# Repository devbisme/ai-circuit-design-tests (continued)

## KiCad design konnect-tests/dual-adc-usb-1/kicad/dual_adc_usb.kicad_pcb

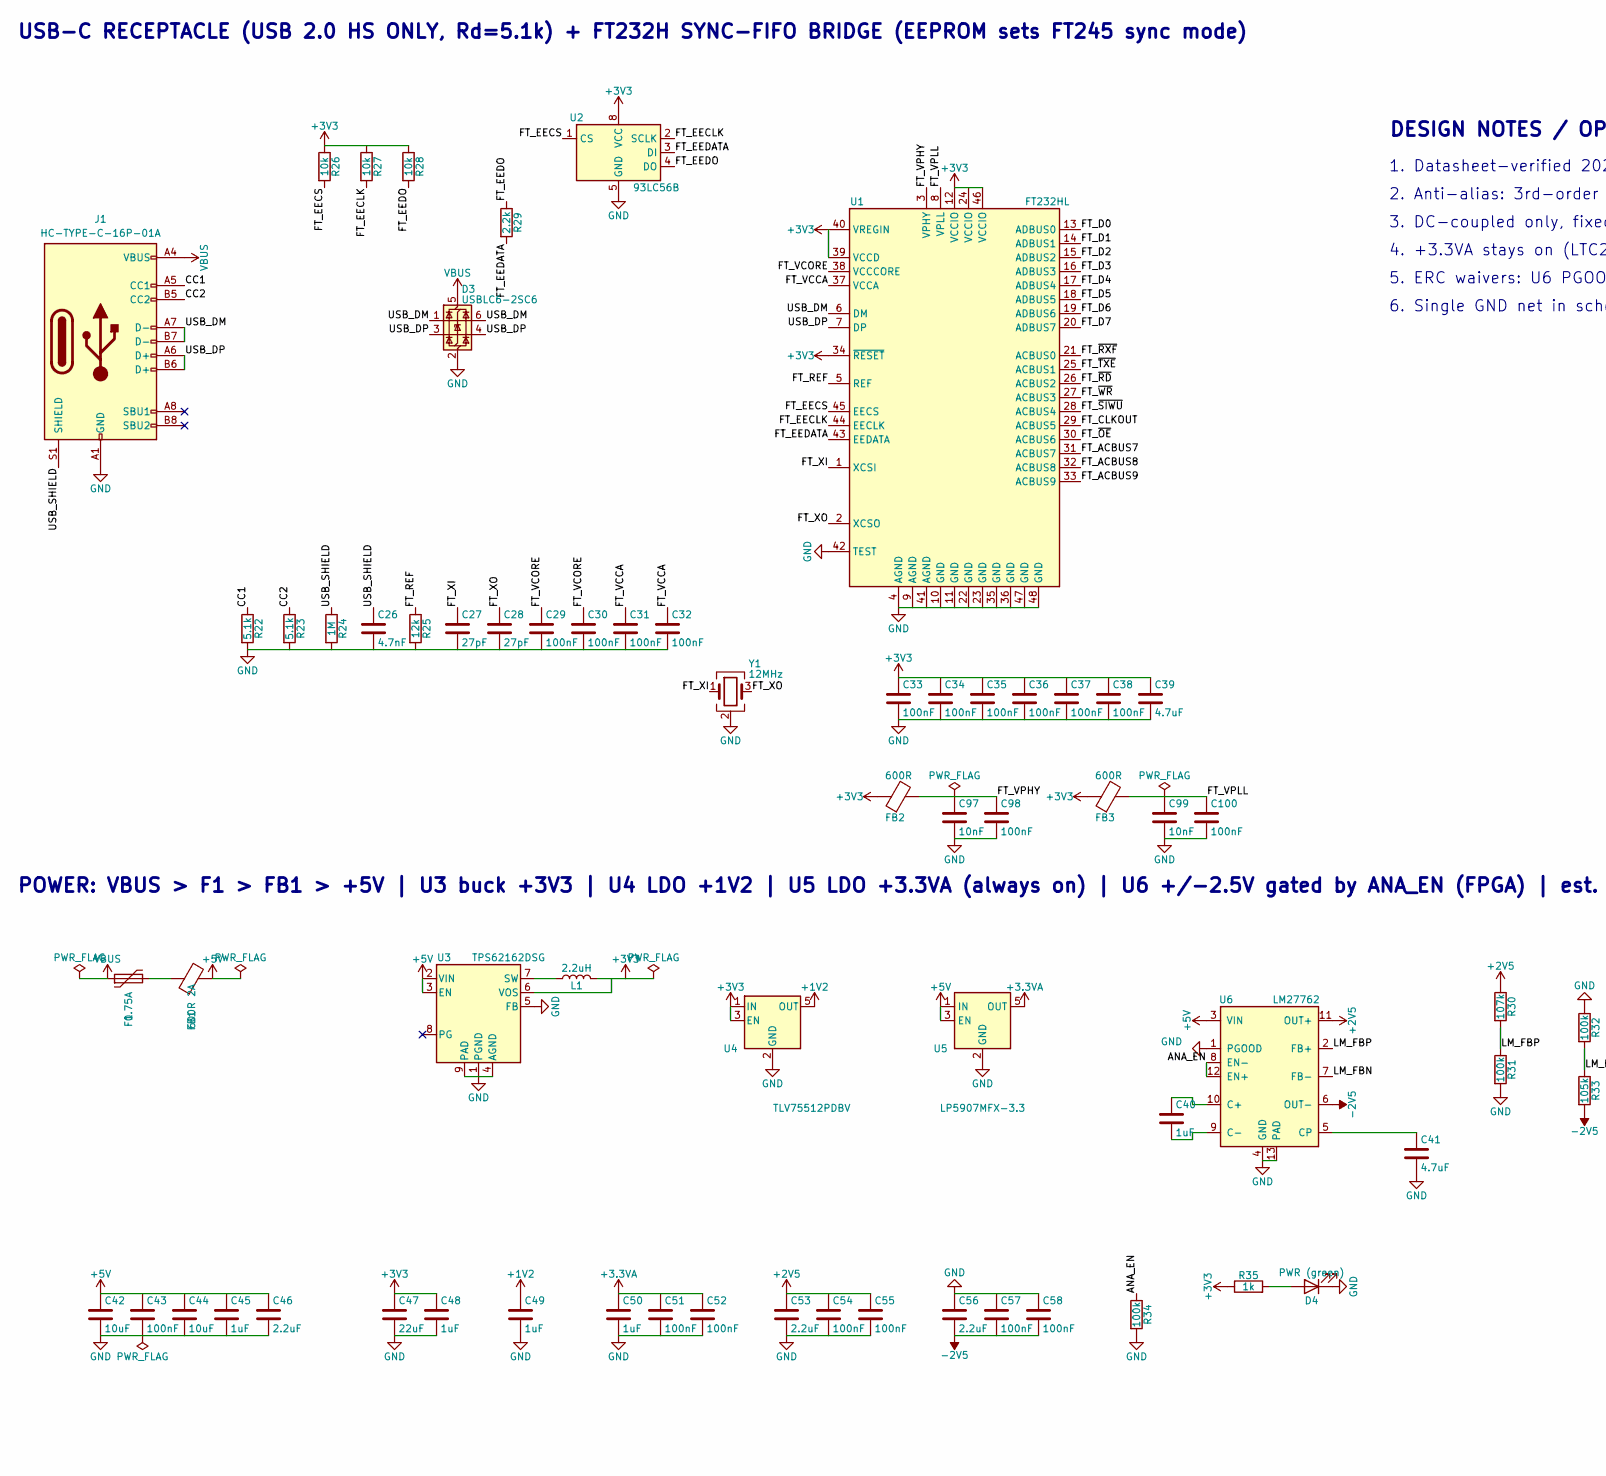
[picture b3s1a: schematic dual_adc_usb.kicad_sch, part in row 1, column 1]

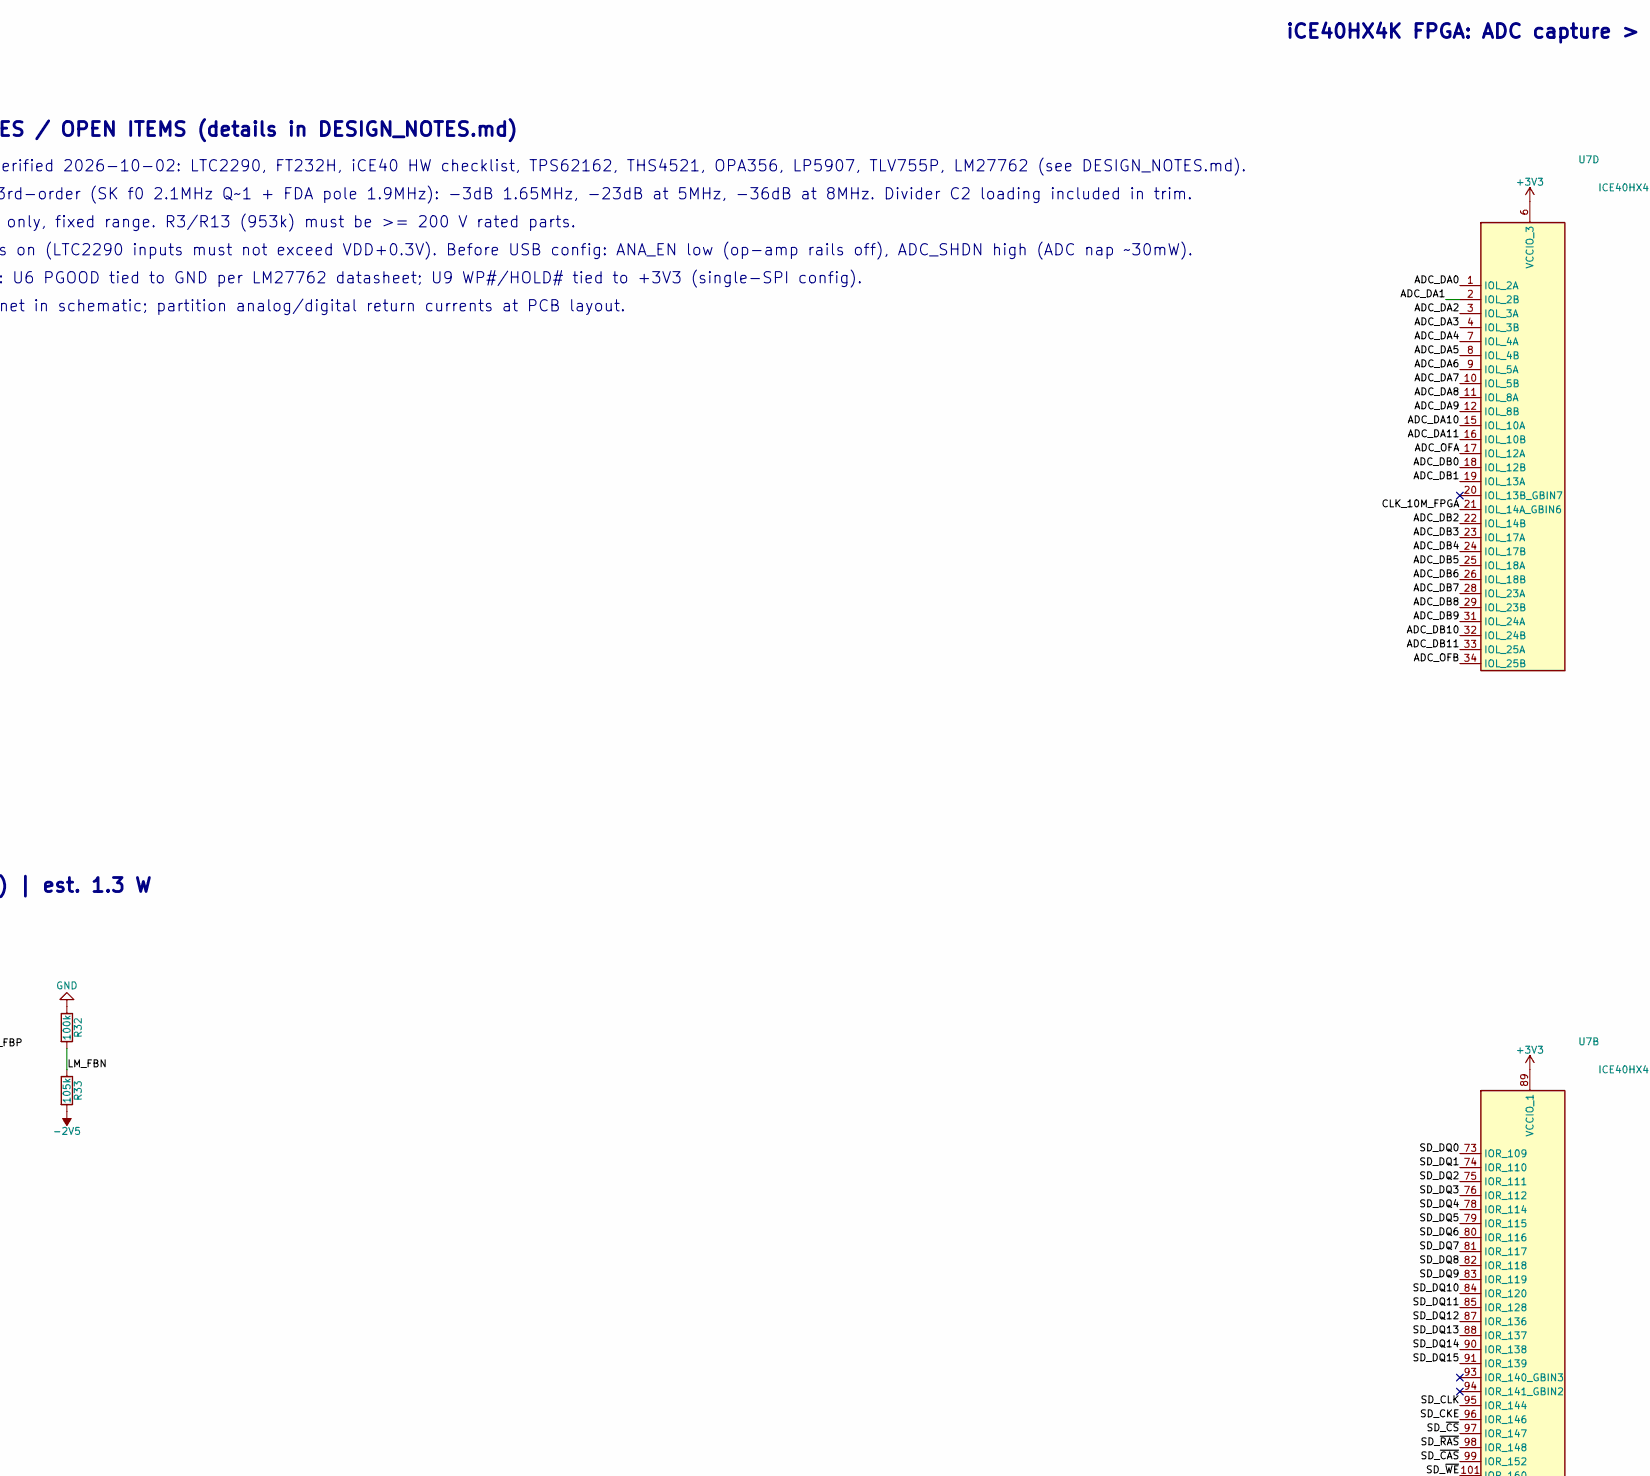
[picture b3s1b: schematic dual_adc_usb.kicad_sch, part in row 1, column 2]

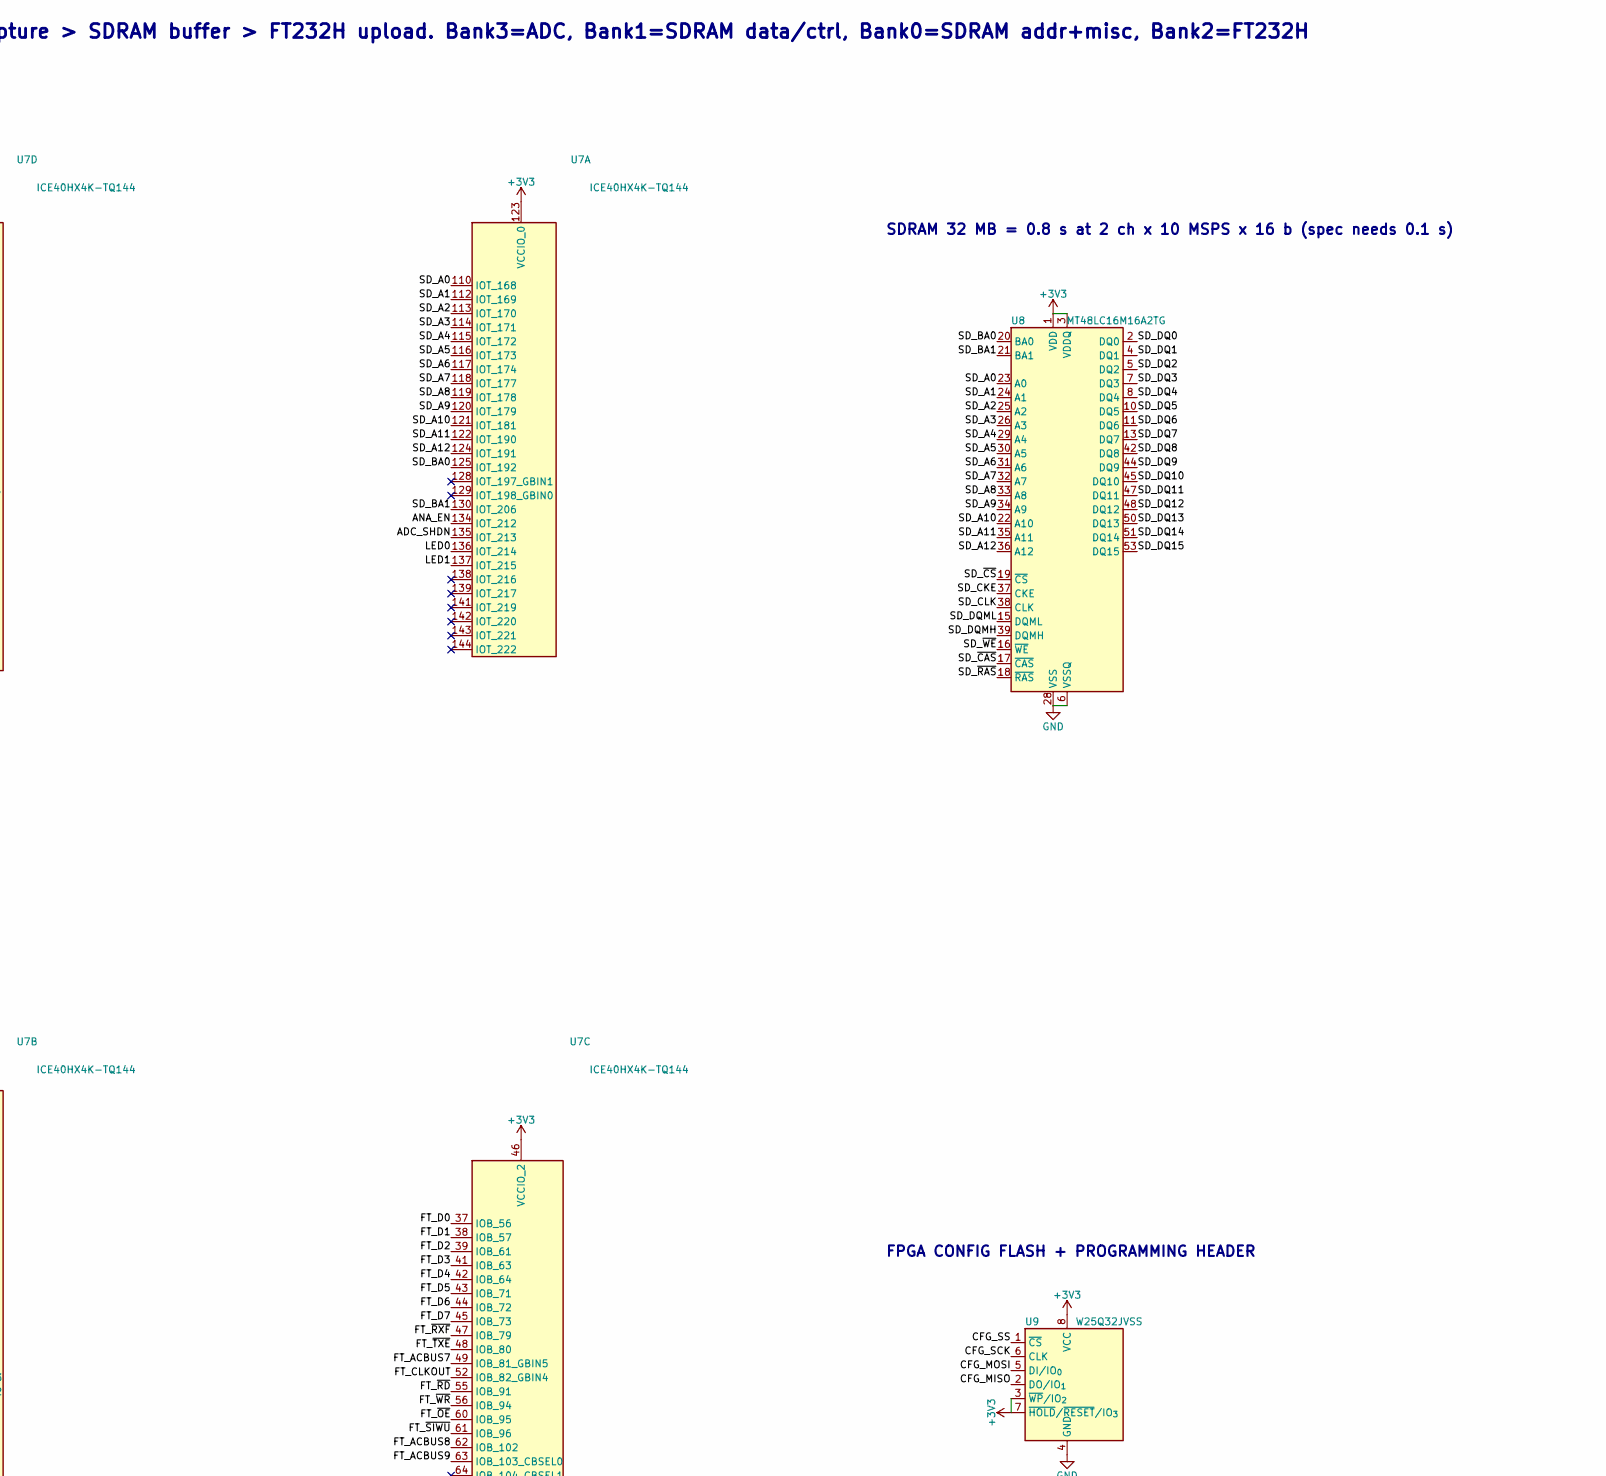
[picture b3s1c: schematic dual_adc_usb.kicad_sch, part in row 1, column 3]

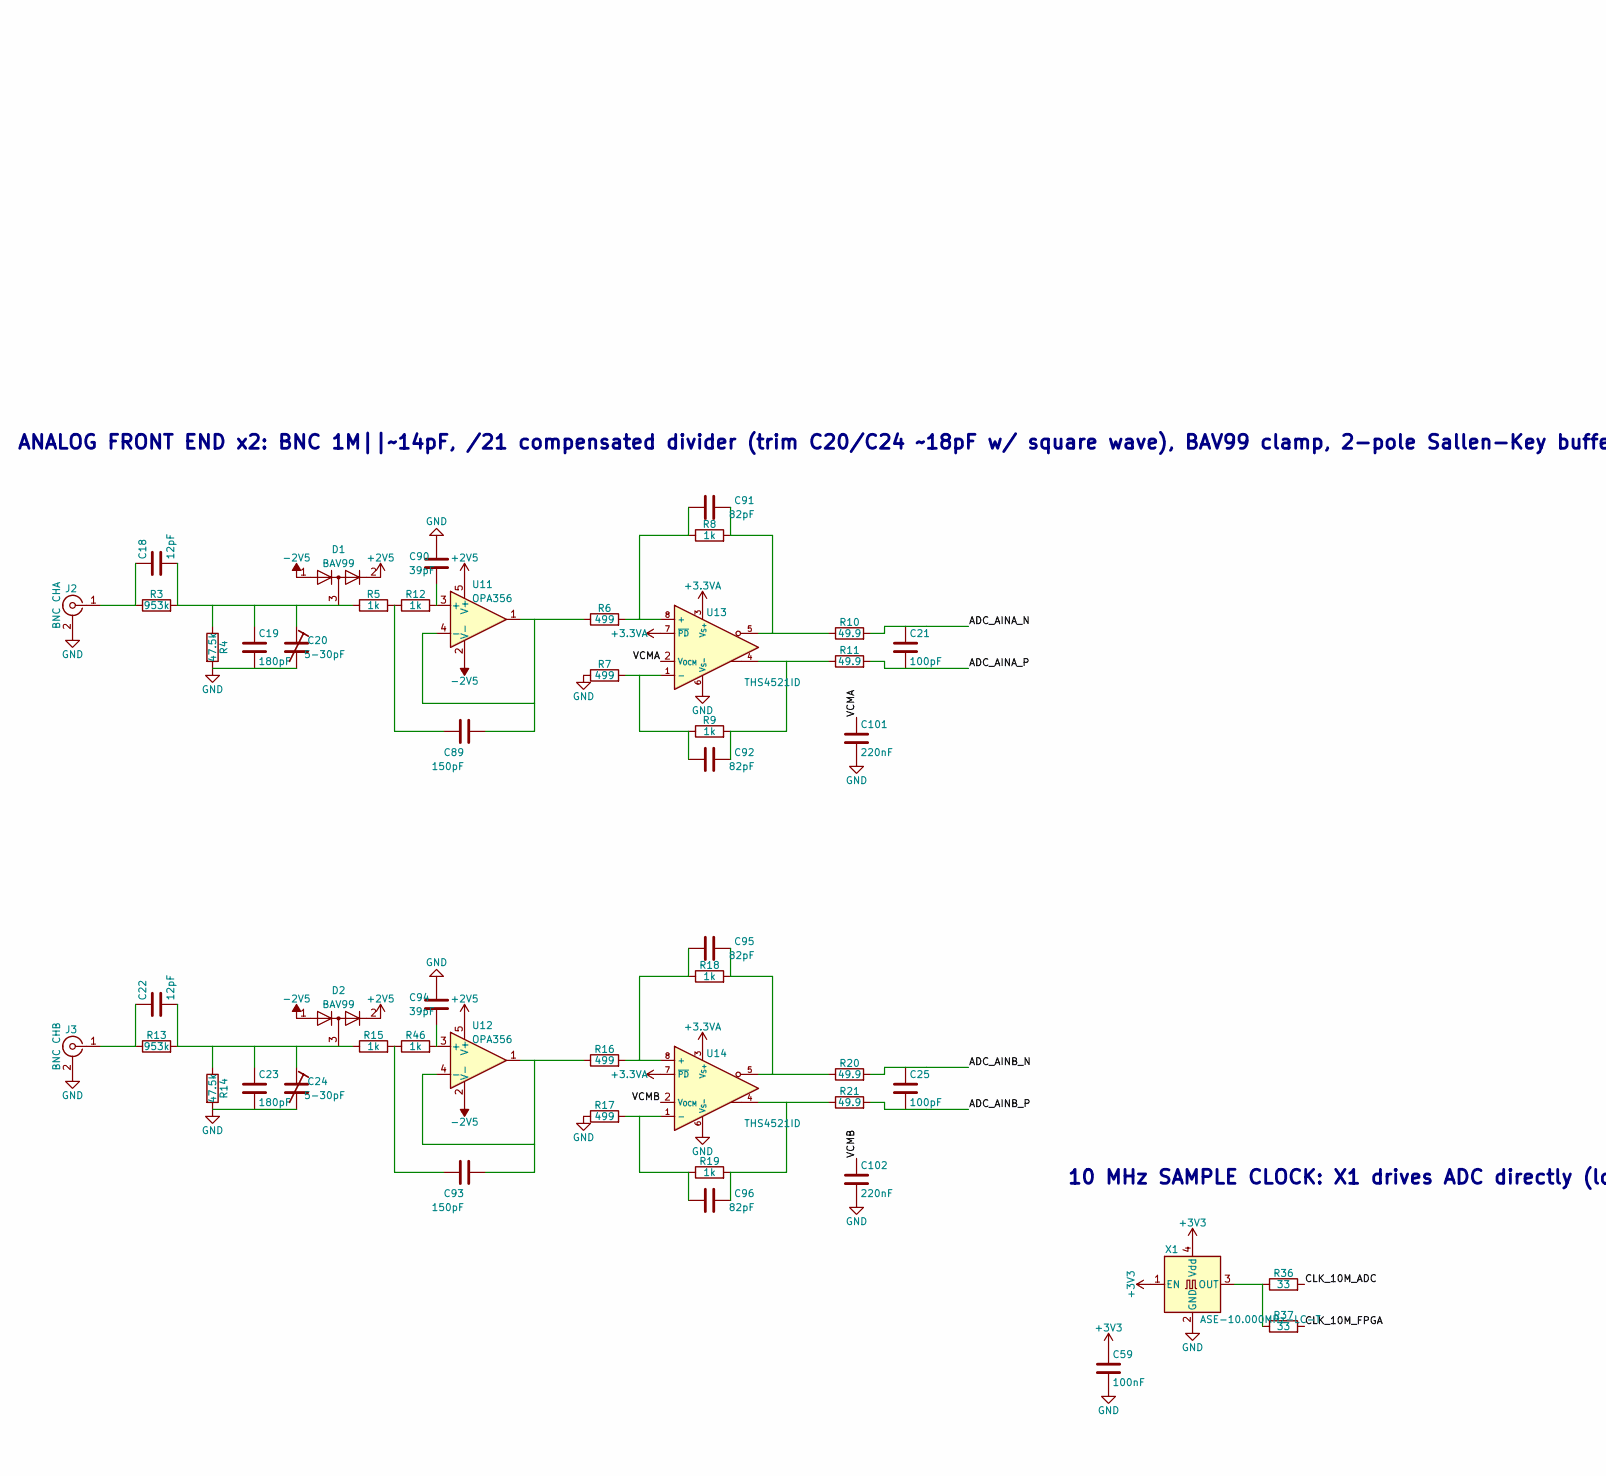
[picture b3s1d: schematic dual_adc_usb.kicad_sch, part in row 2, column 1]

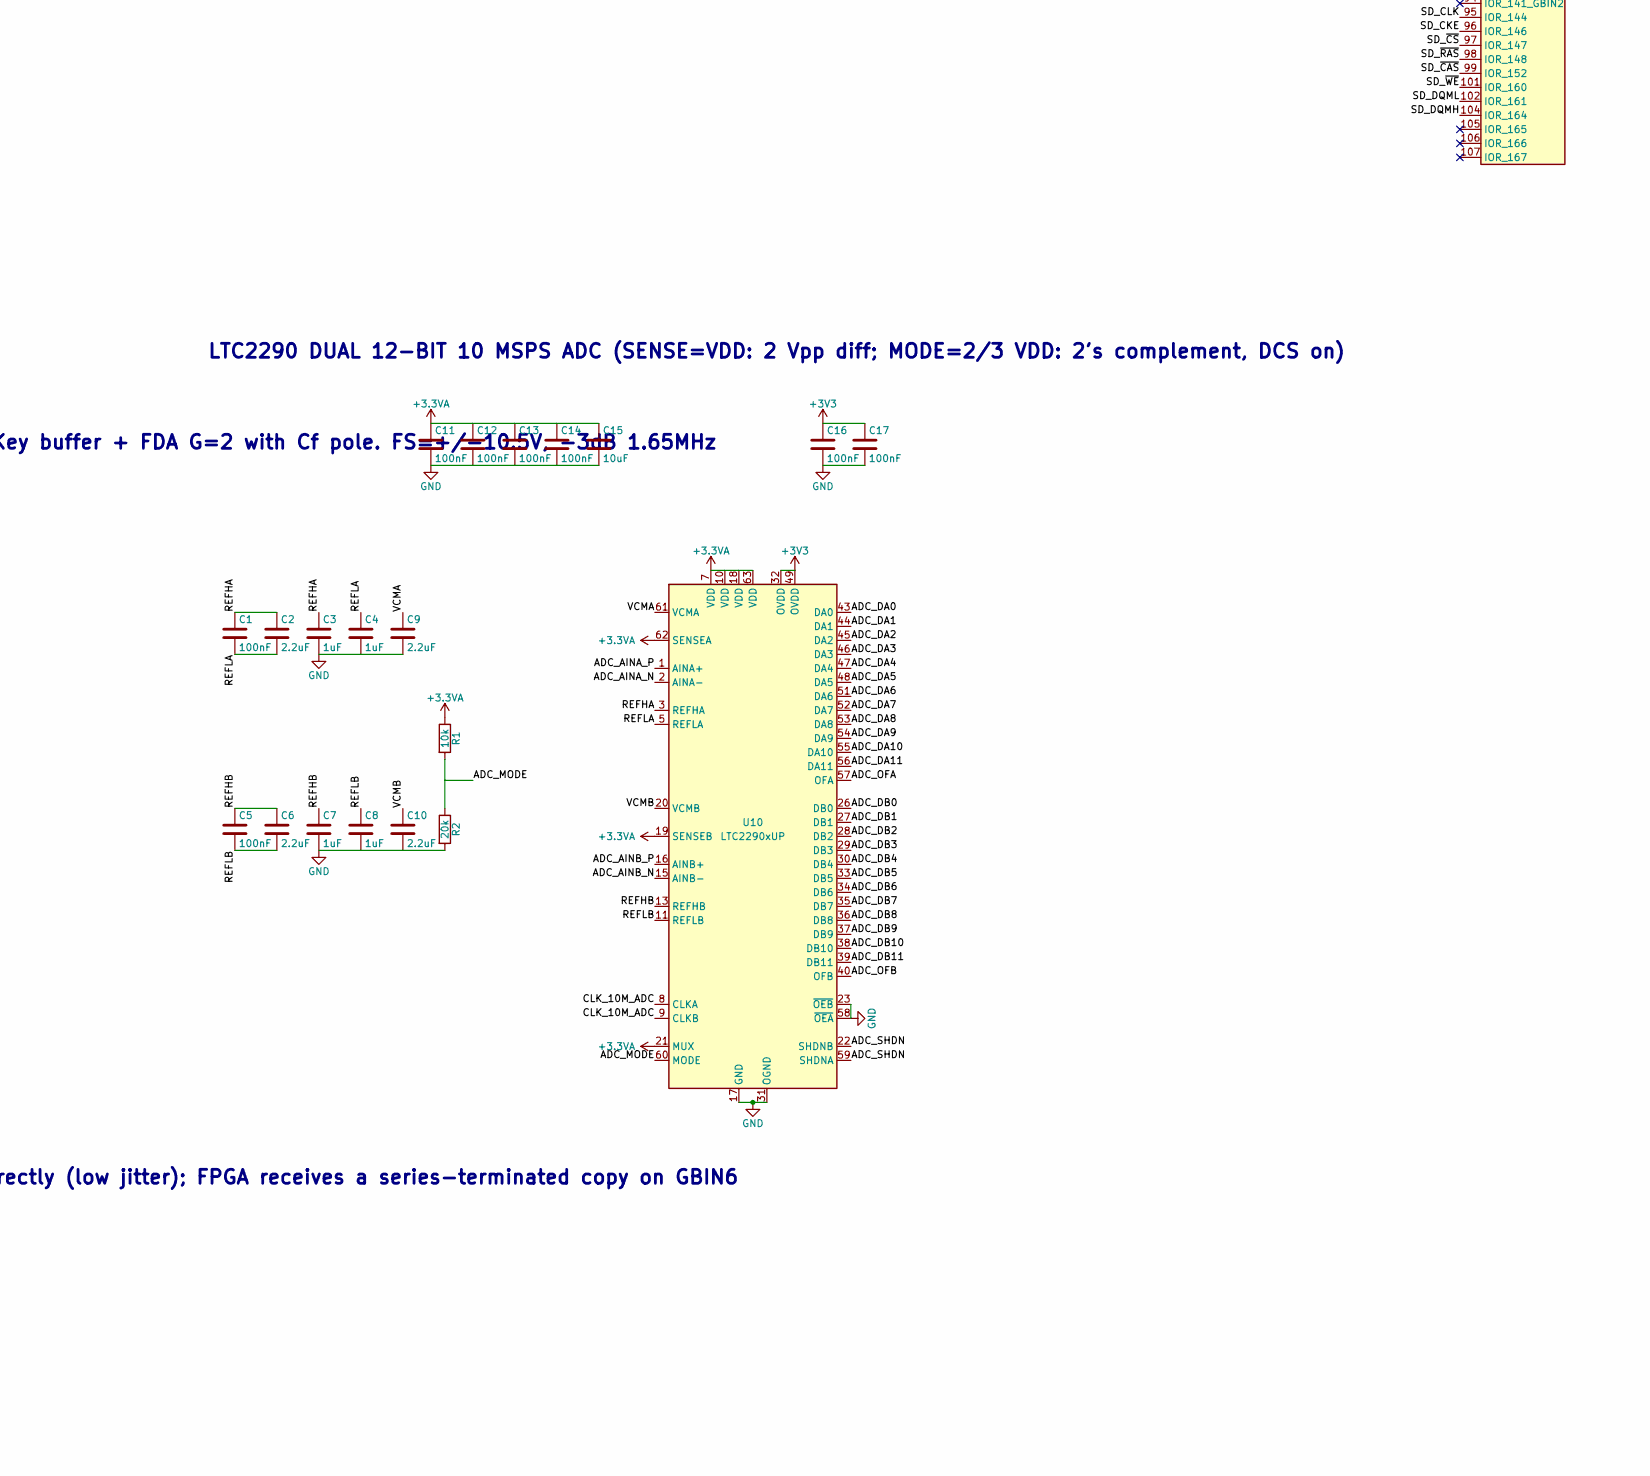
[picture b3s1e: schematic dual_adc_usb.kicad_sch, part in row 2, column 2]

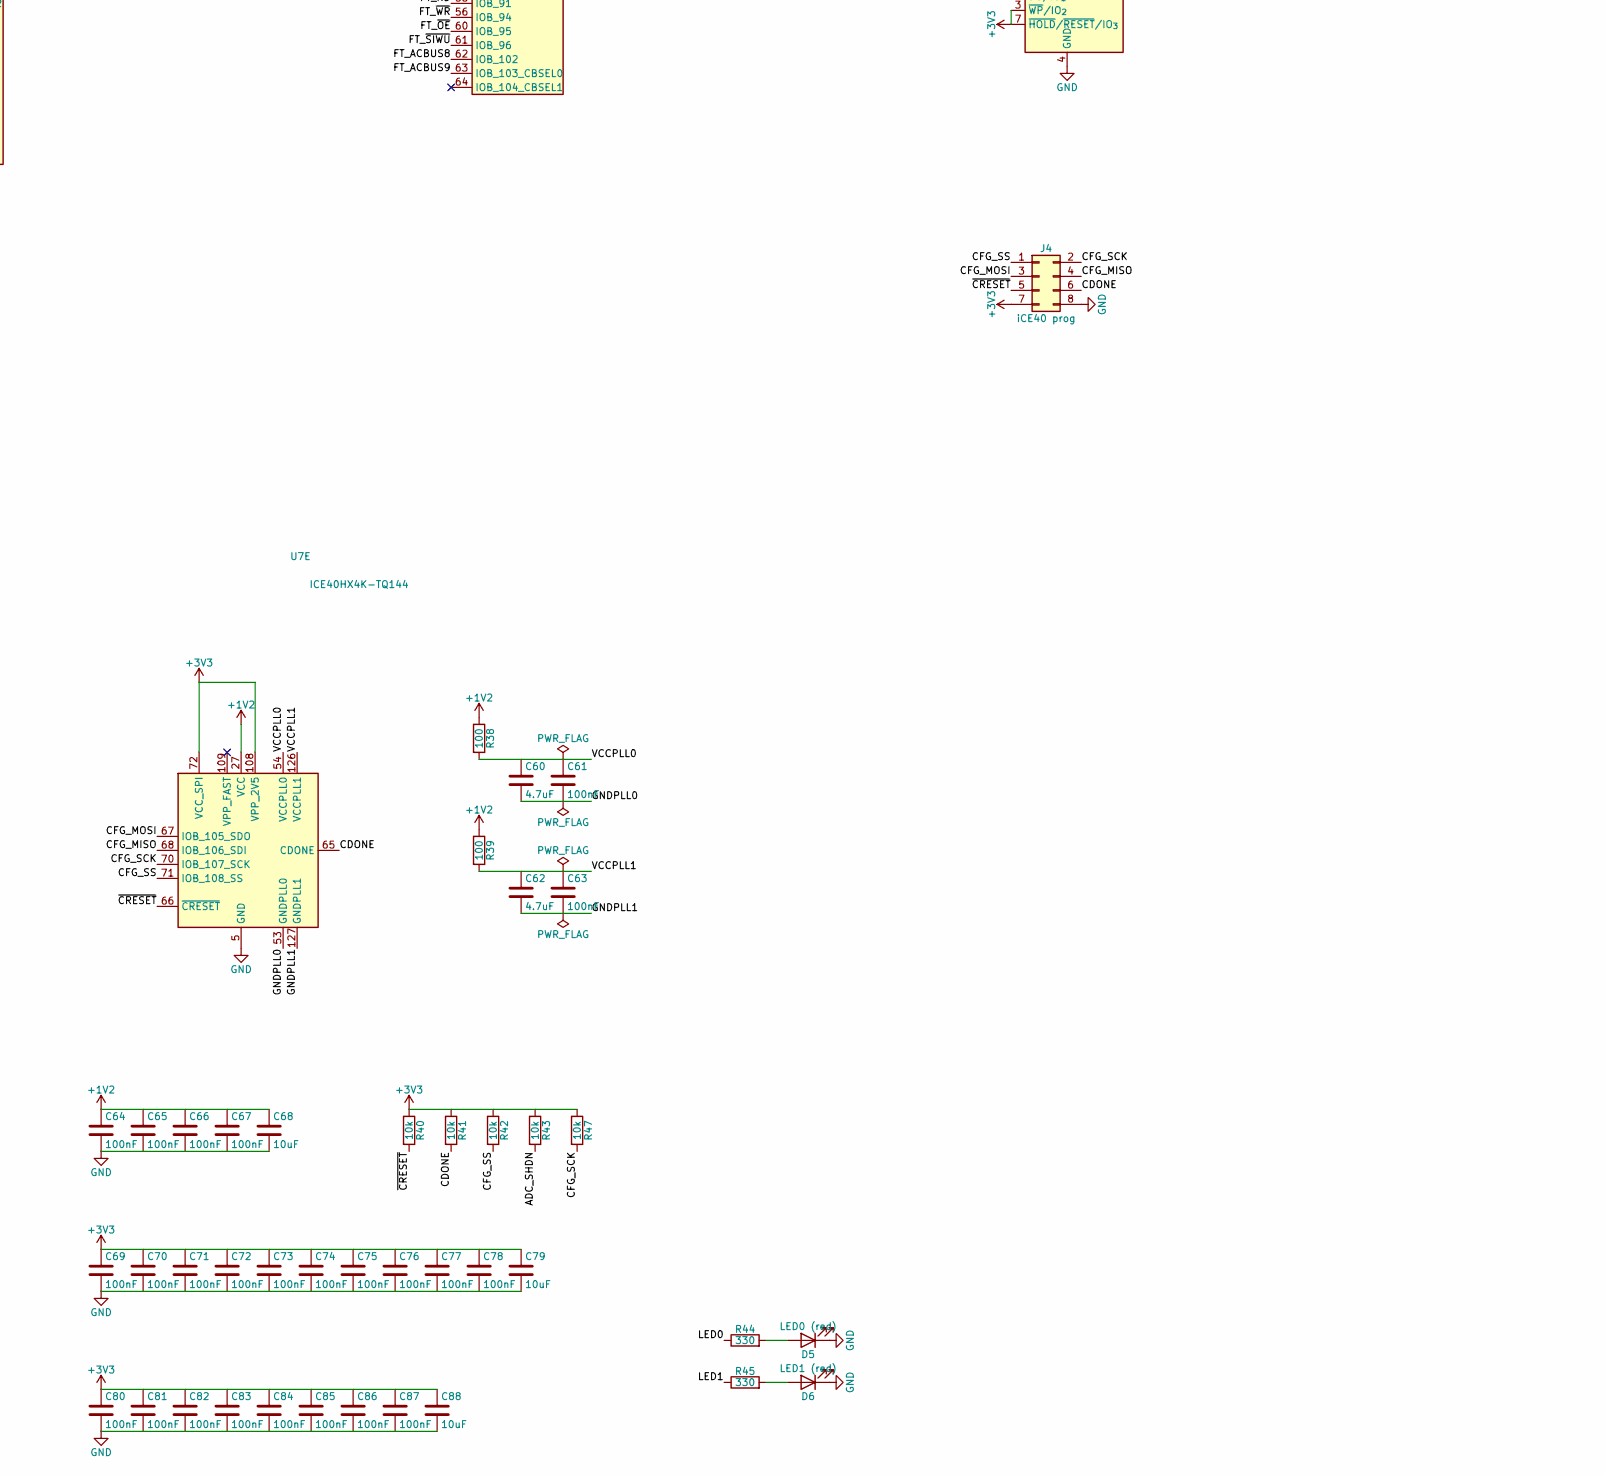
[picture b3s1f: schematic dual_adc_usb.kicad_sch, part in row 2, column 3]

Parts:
C1, C5, C11, C12, C13, C14, C16, C17, C29, C30, C31, C32, C33, C34, C35, C36, C37, C38, C43, C51, C52, C54, C55, C57, C58, C59, C61, C63, C64, C65, C66, C67, C69, C70, C71, C72, C73, C74, C75, C76, C77, C78, C80, C81, C82, C83, C84, C85, C86, C87, C98, C100: 100nF; C_0402_1005Metric
C2, C6, C9, C10, C46, C53, C56: 2.2uF; C_0603_1608Metric
C3, C4, C7, C8, C40, C45, C48, C49, C50: 1uF; C_0603_1608Metric
C15, C42, C44, C68, C79, C88: 10uF; C_0805_2012Metric
C18, C22: 12pF; C_0805_2012Metric; Voltage 100V
C19, C23: 180pF; C_0603_1608Metric
C20, C24: 5-30pF; C_Trimmer_Murata_TZB4-A
C21, C25: 100pF; C_0603_1608Metric
C26: 4.7nF; C_0402_1005Metric
C27, C28: 27pF; C_0402_1005Metric
C39, C41, C60, C62: 4.7uF; C_0603_1608Metric
C47: 22uF; C_0805_2012Metric
C89, C93: 150pF; C_0603_1608Metric
C90, C94: 39pF; C_0603_1608Metric
C91, C92, C95, C96: 82pF; C_0603_1608Metric
C97, C99: 10nF; C_0402_1005Metric
C101, C102: 220nF; C_0402_1005Metric
D1, D2: BAV99; SOT-23
D3: USBLC6-2SC6; SOT-23-6
D4: PWR (green); LED_0603_1608Metric
D5: LED0 (red); LED_0603_1608Metric
D6: LED1 (red); LED_0603_1608Metric
F1: 0.75A; Fuse_1206_3216Metric
FB1: 600R 2A; L_0805_2012Metric
FB2, FB3: 600R; L_0603_1608Metric
J1: HC-TYPE-C-16P-01A; USB_C_Receptacle_HCTL_HC-TYPE-C-16P-01A
J2: BNC CHA; BNC_Amphenol_031-6575_Horizontal
J3: BNC CHB; BNC_Amphenol_031-6575_Horizontal
J4: iCE40 prog; PinHeader_2x04_P2.54mm_Vertical
L1: 2.2uH; L_Taiyo-Yuden_NR-30xx
R1, R26, R27, R28, R40, R41, R42, R43, R47: 10k; R_0402_1005Metric
R2: 20k; R_0402_1005Metric
R3, R13: 953k; R_1206_3216Metric; Tolerance 0.1%; Voltage 200V
R4, R14: 47.5k; R_0603_1608Metric; Tolerance 0.1%
R5, R8, R9, R12, R15, R18, R19, R46: 1k; R_0603_1608Metric; Tolerance 0.1%
R6, R7, R16, R17: 499; R_0603_1608Metric; Tolerance 0.1%
R10, R11, R20, R21: 49.9; R_0603_1608Metric
R22, R23: 5.1k; R_0402_1005Metric
R24: 1M; R_0402_1005Metric
R25: 12k; R_0402_1005Metric; Tolerance 1%
R29: 2.2k; R_0402_1005Metric
R30: 107k; R_0402_1005Metric; Tolerance 1%
R31, R32: 100k; R_0402_1005Metric; Tolerance 1%
R33: 105k; R_0402_1005Metric; Tolerance 1%
R34: 100k; R_0402_1005Metric
R35: 1k; R_0402_1005Metric
R36, R37: 33; R_0402_1005Metric
R38, R39: 100; R_0402_1005Metric
R44, R45: 330; R_0402_1005Metric
U1: FT232HL; LQFP-48_7x7mm_P0.5mm
U2: 93LC56B; SOIC-8_3.9x4.9mm_P1.27mm
U3: TPS62162DSG; WSON-8-1EP_2x2mm_P0.5mm_EP0.9x1.6mm_ThermalVias
U4: TLV75512PDBV; SOT-23-5
U5: LP5907MFX-3.3; SOT-23-5
U6: LM27762; WSON-12-1EP_3x2mm_P0.5mm_EP1x2.65_ThermalVias
U7: ICE40HX4K-TQ144; TQFP-144_20x20mm_P0.5mm
U8: MT48LC16M16A2TG; TSOP-II-54_22.2x10.16mm_P0.8mm
U9: W25Q32JVSS; SOIC-8_5.3x5.3mm_P1.27mm
U10: LTC2290xUP; QFN-64-1EP_9x9mm_P0.5mm_EP7.15x7.15mm
U11, U12: OPA356; SOT-23-5
U13, U14: THS4521ID; SOIC-8_3.9x4.9mm_P1.27mm
X1: ASE-10.000MHz-LC-T; Oscillator_SMD_Abracon_ASE-4Pin_3.2x2.5mm
Y1: 12MHz; Crystal_SMD_3225-4Pin_3.2x2.5mm

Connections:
+1V2: C49.1, C64.1, C65.1, C66.1, C67.1, C68.1, R38.1, R39.1, U4.5 (OUT), U7.27 (VCC), U7.40 (VCC), U7.92 (VCC), U7.111 (VCC)
+2V5: C53.1, C54.1, C55.1, D1.2 (A), D2.2 (A), R30.1, U6.11 (OUT+), U11.5 (V+), U12.5 (V+)
+3.3VA: C11.1, C12.1, C13.1, C14.1, C15.1, C50.1, C51.1, C52.1, R1.1, U5.5 (OUT), U10.7 (VDD), U10.10 (VDD), U10.18 (VDD), U10.19 (SENSEB), U10.21 (MUX), U10.62 (SENSEA), U10.63 (VDD), U13.3 (V_{S+}), U13.7 (~PD), U14.3 (V_{S+}), U14.7 (~PD)
-2V5: C56.2, C57.2, C58.2, D1.1 (K), D2.1 (K), R33.2, U6.6 (OUT-), U11.2 (V-), U12.2 (V-)
/ADC_AINA_N: C21.1, R10.2, U10.2 (AINA-)
/ADC_AINA_P: C21.2, R11.2, U10.1 (AINA+)
/ADC_AINB_N: C25.1, R20.2, U10.15 (AINB-)
/ADC_AINB_P: C25.2, R21.2, U10.16 (AINB+)
/ADC_DA0: U7.1 (IOL_2A), U10.43 (DA0)
/ADC_DA1: U7.2 (IOL_2B), U10.44 (DA1)
/ADC_DA2: U7.3 (IOL_3A), U10.45 (DA2)
/ADC_DA3: U7.4 (IOL_3B), U10.46 (DA3)
/ADC_DA4: U7.7 (IOL_4A), U10.47 (DA4)
/ADC_DA5: U7.8 (IOL_4B), U10.48 (DA5)
/ADC_DA6: U7.9 (IOL_5A), U10.51 (DA6)
/ADC_DA7: U7.10 (IOL_5B), U10.52 (DA7)
/ADC_DA8: U7.11 (IOL_8A), U10.53 (DA8)
/ADC_DA9: U7.12 (IOL_8B), U10.54 (DA9)
/ADC_DA10: U7.15 (IOL_10A), U10.55 (DA10)
/ADC_DA11: U7.16 (IOL_10B), U10.56 (DA11)
/ADC_DB0: U7.18 (IOL_12B), U10.26 (DB0)
/ADC_DB1: U7.19 (IOL_13A), U10.27 (DB1)
/ADC_DB2: U7.22 (IOL_14B), U10.28 (DB2)
/ADC_DB3: U7.23 (IOL_17A), U10.29 (DB3)
/ADC_DB4: U7.24 (IOL_17B), U10.30 (DB4)
/ADC_DB5: U7.25 (IOL_18A), U10.33 (DB5)
/ADC_DB6: U7.26 (IOL_18B), U10.34 (DB6)
/ADC_DB7: U7.28 (IOL_23A), U10.35 (DB7)
/ADC_DB8: U7.29 (IOL_23B), U10.36 (DB8)
/ADC_DB9: U7.31 (IOL_24A), U10.37 (DB9)
/ADC_DB10: U7.32 (IOL_24B), U10.38 (DB10)
/ADC_DB11: U7.33 (IOL_25A), U10.39 (DB11)
/ADC_MODE: R1.2, R2.1, U10.60 (MODE)
/ADC_OFA: U7.17 (IOL_12A), U10.57 (OFA)
/ADC_OFB: U7.34 (IOL_25B), U10.40 (OFB)
/ADC_SHDN: R43.2, U7.135 (IOT_213), U10.22 (SHDNB), U10.59 (SHDNA)
/ANA_EN: R34.1, U6.8 (EN-), U6.12 (EN+), U7.134 (IOT_212)
/CC1: J1.A5 (CC1), R22.1
/CC2: J1.B5 (CC2), R23.1
/CDONE: J4.6, R41.2, U7.65 (CDONE)
/CFG_MISO: J4.4, U7.68 (IOB_106_SDI), U9.2 (DO/IO_{1})
/CFG_MOSI: J4.3, U7.67 (IOB_105_SDO), U9.5 (DI/IO_{0})
/CFG_SCK: J4.2, R47.2, U7.70 (IOB_107_SCK), U9.6 (CLK)
/CFG_SS: J4.1, R42.2, U7.71 (IOB_108_SS), U9.1 (~CS)
/CLK_10M_ADC: R36.2, U10.8 (CLKA), U10.9 (CLKB)
/CLK_10M_FPGA: R37.2, U7.21 (IOL_14A_GBIN6)
/FT_ACBUS7: U1.31 (ACBUS7), U7.49 (IOB_81_GBIN5)
/FT_ACBUS8: U1.32 (ACBUS8), U7.62 (IOB_102)
/FT_ACBUS9: U1.33 (ACBUS9), U7.63 (IOB_103_CBSEL0)
/FT_CLKOUT: U1.29 (ACBUS5), U7.52 (IOB_82_GBIN4)
/FT_D0: U1.13 (ADBUS0), U7.37 (IOB_56)
/FT_D1: U1.14 (ADBUS1), U7.38 (IOB_57)
/FT_D2: U1.15 (ADBUS2), U7.39 (IOB_61)
/FT_D3: U1.16 (ADBUS3), U7.41 (IOB_63)
/FT_D4: U1.17 (ADBUS4), U7.42 (IOB_64)
/FT_D5: U1.18 (ADBUS5), U7.43 (IOB_71)
/FT_D6: U1.19 (ADBUS6), U7.44 (IOB_72)
/FT_D7: U1.20 (ADBUS7), U7.45 (IOB_73)
/FT_EECLK: R27.2, U1.44 (EECLK), U2.2 (SCLK)
/FT_EECS: R26.2, U1.45 (EECS), U2.1 (CS)
/FT_EEDATA: R29.2, U1.43 (EEDATA), U2.3 (DI)
/FT_EEDO: R28.2, R29.1, U2.4 (DO)
/FT_REF: R25.1, U1.5 (REF)
/FT_VCCA: C31.1, C32.1, U1.37 (VCCA)
/FT_VCORE: C29.1, C30.1, U1.38 (VCCCORE)
/FT_XI: C27.1, U1.1 (XCSI), Y1.1
/FT_XO: C28.1, U1.2 (XCSO), Y1.3
/FT_~OE: U1.30 (ACBUS6), U7.60 (IOB_95)
/FT_~RD: U1.26 (ACBUS2), U7.55 (IOB_91)
/FT_~RXF: U1.21 (ACBUS0), U7.47 (IOB_79)
/FT_~SIWU: U1.28 (ACBUS4), U7.61 (IOB_96)
/FT_~TXE: U1.25 (ACBUS1), U7.48 (IOB_80)
/FT_~WR: U1.27 (ACBUS3), U7.56 (IOB_94)
/LED0: R44.1, U7.136 (IOT_214)
/LED1: R45.1, U7.137 (IOT_215)
/LM_FBN: R32.2, R33.1, U6.7 (FB-)
/LM_FBP: R30.2, R31.1, U6.2 (FB+)
/REFHA: C1.1, C2.1, C3.1, U10.3 (REFHA), U10.4 (REFHA)
/REFHB: C5.1, C6.1, C7.1, U10.13 (REFHB), U10.14 (REFHB)
/REFLA: C1.2, C2.2, C4.1, U10.5 (REFLA), U10.6 (REFLA)
/REFLB: C5.2, C6.2, C8.1, U10.11 (REFLB), U10.12 (REFLB)
/SD_A0: U7.110 (IOT_168), U8.23 (A0)
/SD_A1: U7.112 (IOT_169), U8.24 (A1)
/SD_A2: U7.113 (IOT_170), U8.25 (A2)
/SD_A3: U7.114 (IOT_171), U8.26 (A3)
/SD_A4: U7.115 (IOT_172), U8.29 (A4)
/SD_A5: U7.116 (IOT_173), U8.30 (A5)
/SD_A6: U7.117 (IOT_174), U8.31 (A6)
/SD_A7: U7.118 (IOT_177), U8.32 (A7)
/SD_A8: U7.119 (IOT_178), U8.33 (A8)
/SD_A9: U7.120 (IOT_179), U8.34 (A9)
/SD_A10: U7.121 (IOT_181), U8.22 (A10)
/SD_A11: U7.122 (IOT_190), U8.35 (A11)
/SD_A12: U7.124 (IOT_191), U8.36 (A12)
/SD_BA0: U7.125 (IOT_192), U8.20 (BA0)
/SD_BA1: U7.130 (IOT_206), U8.21 (BA1)
/SD_CKE: U7.96 (IOR_146), U8.37 (CKE)
/SD_CLK: U7.95 (IOR_144), U8.38 (CLK)
/SD_DQ0: U7.73 (IOR_109), U8.2 (DQ0)
/SD_DQ1: U7.74 (IOR_110), U8.4 (DQ1)
/SD_DQ2: U7.75 (IOR_111), U8.5 (DQ2)
/SD_DQ3: U7.76 (IOR_112), U8.7 (DQ3)
/SD_DQ4: U7.78 (IOR_114), U8.8 (DQ4)
/SD_DQ5: U7.79 (IOR_115), U8.10 (DQ5)
/SD_DQ6: U7.80 (IOR_116), U8.11 (DQ6)
/SD_DQ7: U7.81 (IOR_117), U8.13 (DQ7)
/SD_DQ8: U7.82 (IOR_118), U8.42 (DQ8)
/SD_DQ9: U7.83 (IOR_119), U8.44 (DQ9)
/SD_DQ10: U7.84 (IOR_120), U8.45 (DQ10)
/SD_DQ11: U7.85 (IOR_128), U8.47 (DQ11)
/SD_DQ12: U7.87 (IOR_136), U8.48 (DQ12)
/SD_DQ13: U7.88 (IOR_137), U8.50 (DQ13)
/SD_DQ14: U7.90 (IOR_138), U8.51 (DQ14)
/SD_DQ15: U7.91 (IOR_139), U8.53 (DQ15)
/SD_DQMH: U7.104 (IOR_164), U8.39 (DQMH)
/SD_DQML: U7.102 (IOR_161), U8.15 (DQML)
/SD_~CAS: U7.99 (IOR_152), U8.17 (~CAS)
/SD_~CS: U7.97 (IOR_147), U8.19 (~CS)
/SD_~RAS: U7.98 (IOR_148), U8.18 (~RAS)
/SD_~WE: U7.101 (IOR_160), U8.16 (~WE)
/USB_DM: D3.1 (I/O1), D3.6 (I/O1), J1.A7 (D-), J1.B7 (D-), U1.6 (DM)
/USB_DP: D3.3 (I/O2), D3.4 (I/O2), J1.A6 (D+), J1.B6 (D+), U1.7 (DP)
/USB_SHIELD: C26.1, J1.S1 (SHIELD), R24.1
/VCMA: C9.1, C101.1, U10.61 (VCMA), U13.2 (V_{OCM})
/VCMB: C10.1, C102.1, U10.20 (VCMB), U14.2 (V_{OCM})
/~CRESET: J4.5, R40.2, U7.66 (~CRESET)
unnamed: C18.2, C19.1, C20.1, D1.3 (K), R3.2, R4.1, R5.1
unnamed: C22.2, C23.1, C24.1, D2.3 (K), R13.2, R14.1, R15.1
unnamed: C89.1, R5.2, R12.1
unnamed: C91.2, R8.2, R10.1, U13.5
unnamed: C92.2, R9.2, R11.1, U13.4
unnamed: C93.1, R15.2, R46.1
unnamed: C95.2, R18.2, R20.1, U14.5
unnamed: C96.2, R19.2, R21.1, U14.4
unnamed: D4.2 (A), R35.2
unnamed: D5.2 (A), R44.2
unnamed: D6.2 (A), R45.2
unnamed: F1.2, FB1.1
unnamed: C18.1, J2.1 (In), R3.1
unnamed: C22.1, J3.1 (In), R13.1
unnamed: L1.1, U3.7 (SW)
unnamed: C40.1, U6.10 (C+)
unnamed: C40.2, U6.9 (C-)
unnamed: C41.1, U6.5 (CP)
unnamed: C90.2, R12.2, U11.3 (+)
unnamed: C89.2, R6.1, U11.1, U11.4 (-)
unnamed: C94.2, R46.2, U12.3 (+)
unnamed: C93.2, R16.1, U12.1, U12.4 (-)
unnamed: C91.1, R6.2, R8.1, U13.8 (+)
unnamed: C92.1, R7.2, R9.1, U13.1 (-)
unnamed: C95.1, R16.2, R18.1, U14.8 (+)
unnamed: C96.1, R17.2, R19.1, U14.1 (-)
unnamed: R36.1, R37.1, X1.3 (OUT)

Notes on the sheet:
USB-C RECEPTACLE (USB 2.0 HS ONLY, Rd=5.1k) + FT232H SYNC-FIFO BRIDGE (EEPROM sets FT245 sync mode)
LTC2290 DUAL 12-BIT 10 MSPS ADC (SENSE=VDD: 2 Vpp diff; MODE=2/3 VDD: 2's complement, DCS on)
10 MHz SAMPLE CLOCK: X1 drives ADC directly (low jitter); FPGA receives a series-terminated copy on GBIN6
iCE40HX4K FPGA: ADC capture > SDRAM buffer > FT232H upload. Bank3=ADC, Bank1=SDRAM data/ctrl, Bank0=SDRAM addr+misc, Bank2=FT232H
SDRAM 32 MB = 0.8 s at 2 ch x 10 MSPS x 16 b (spec needs 0.1 s)
FPGA CONFIG FLASH + PROGRAMMING HEADER
DESIGN NOTES / OPEN ITEMS (details in DESIGN_NOTES.md)
3. DC-coupled only, fixed range. R3/R13 (953k) must be >= 200 V rated parts.
5. ERC waivers: U6 PGOOD tied to GND per LM27762 datasheet; U9 WP#/HOLD# tied to +3V3 (single-SPI config).
6. Single GND net in schematic; partition analog/digital return currents at PCB layout.
ANALOG FRONT END x2: BNC 1M||~14pF, /21 compensated divider (trim C20/C24 ~18pF w/ square wave), BAV99 clamp, 2-pole Sallen-Key buffer + FDA G=2 with Cf pole. FS=+/-10.5V, -3dB 1.65MHz
2. Anti-alias: 3rd-order (SK f0 2.1MHz Q~1 + FDA pole 1.9MHz): -3dB 1.65MHz, -23dB at 5MHz, -36dB at 8MHz. Divider C2 loading included in trim.
POWER: VBUS > F1 > FB1 > +5V | U3 buck +3V3 | U4 LDO +1V2 | U5 LDO +3.3VA (always on) | U6 +/-2.5V gated by ANA_EN (FPGA) | est. 1.3 W
1. Datasheet-verified 2026-10-02: LTC2290, FT232H, iCE40 HW checklist, TPS62162, THS4521, OPA356, LP5907, TLV755P, LM27762 (see DESIGN_NOTES.md).
4. +3.3VA stays on (LTC2290 inputs must not exceed VDD+0.3V). Before USB config: ANA_EN low (op-amp rails off), ADC_SHDN high (ADC nap ~30mW).

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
